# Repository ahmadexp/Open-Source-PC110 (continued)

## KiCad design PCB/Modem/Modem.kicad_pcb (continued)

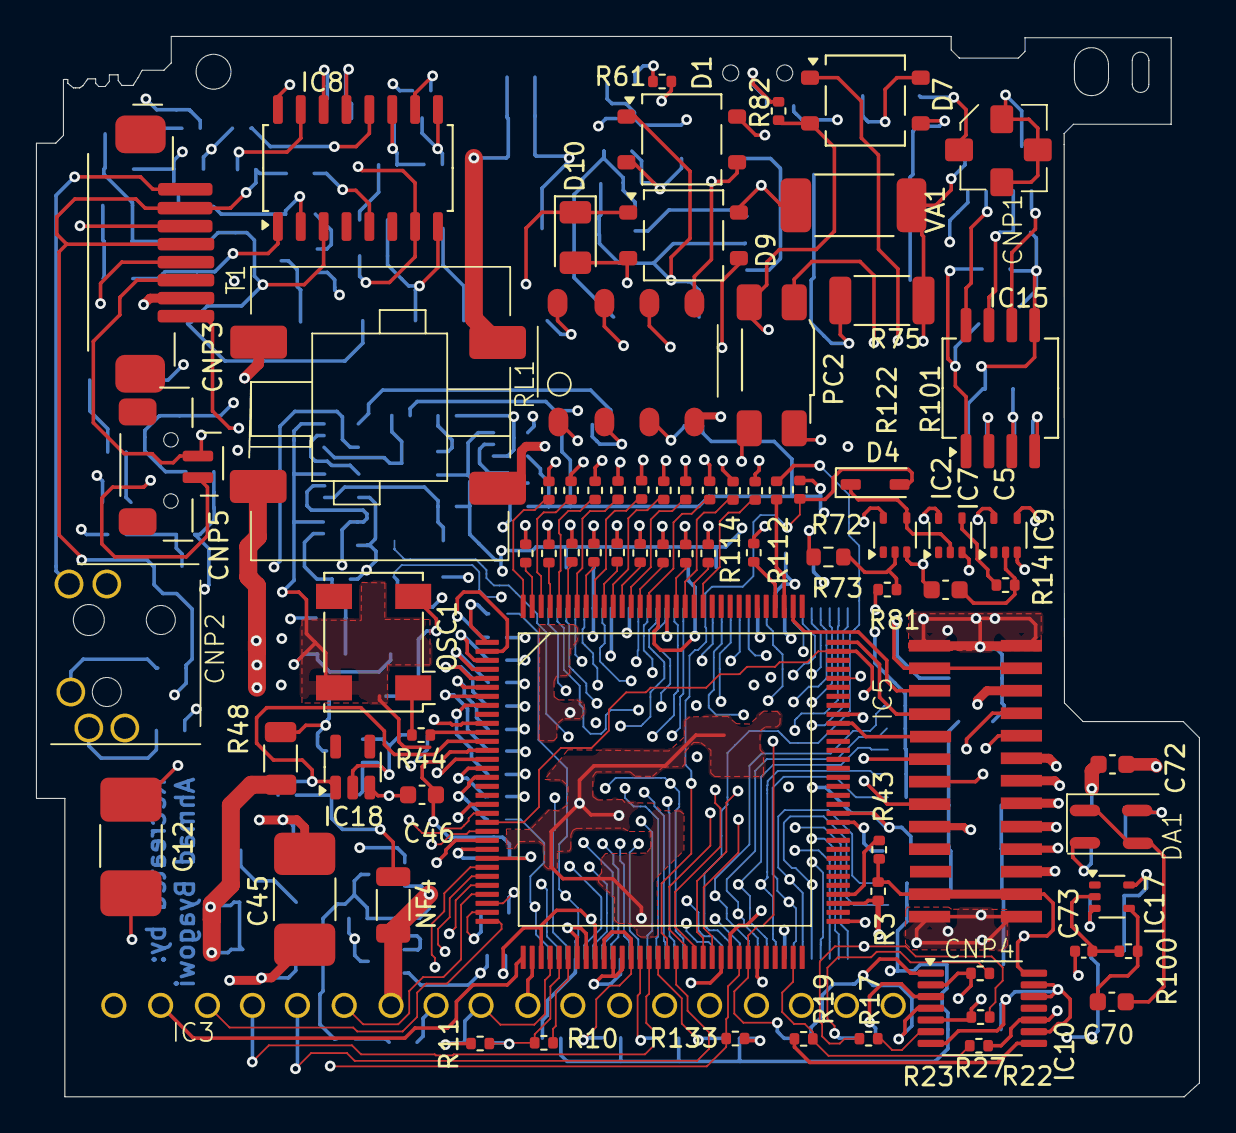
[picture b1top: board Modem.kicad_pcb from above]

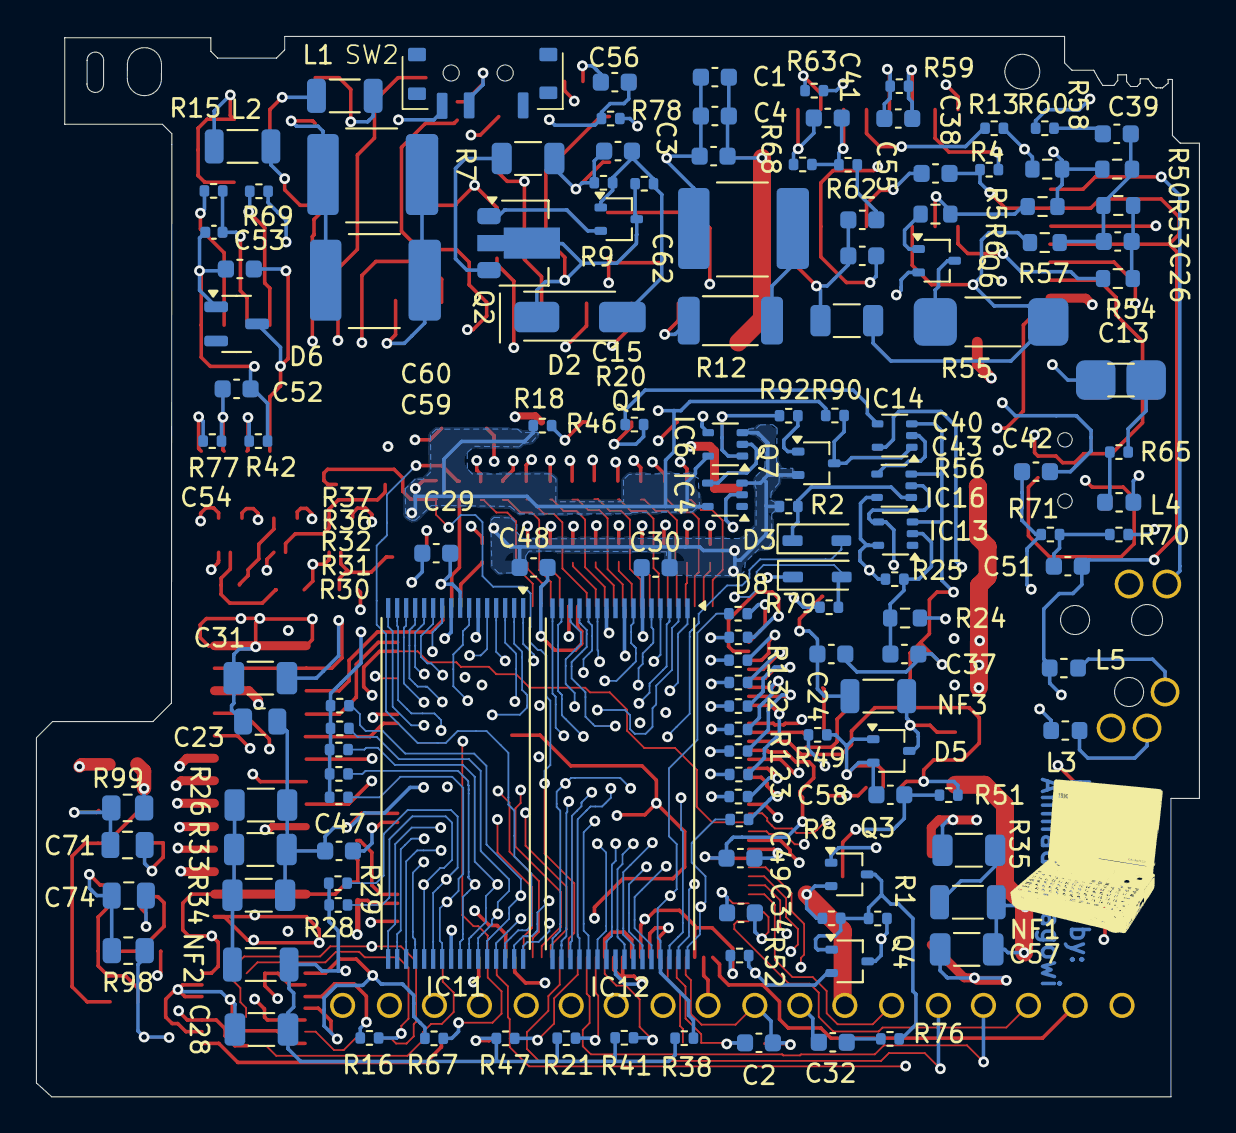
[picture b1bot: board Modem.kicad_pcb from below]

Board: 6 copper layers, 64.6 x 58.9 mm, 211 parts (136 on the bottom side), 206 nets.

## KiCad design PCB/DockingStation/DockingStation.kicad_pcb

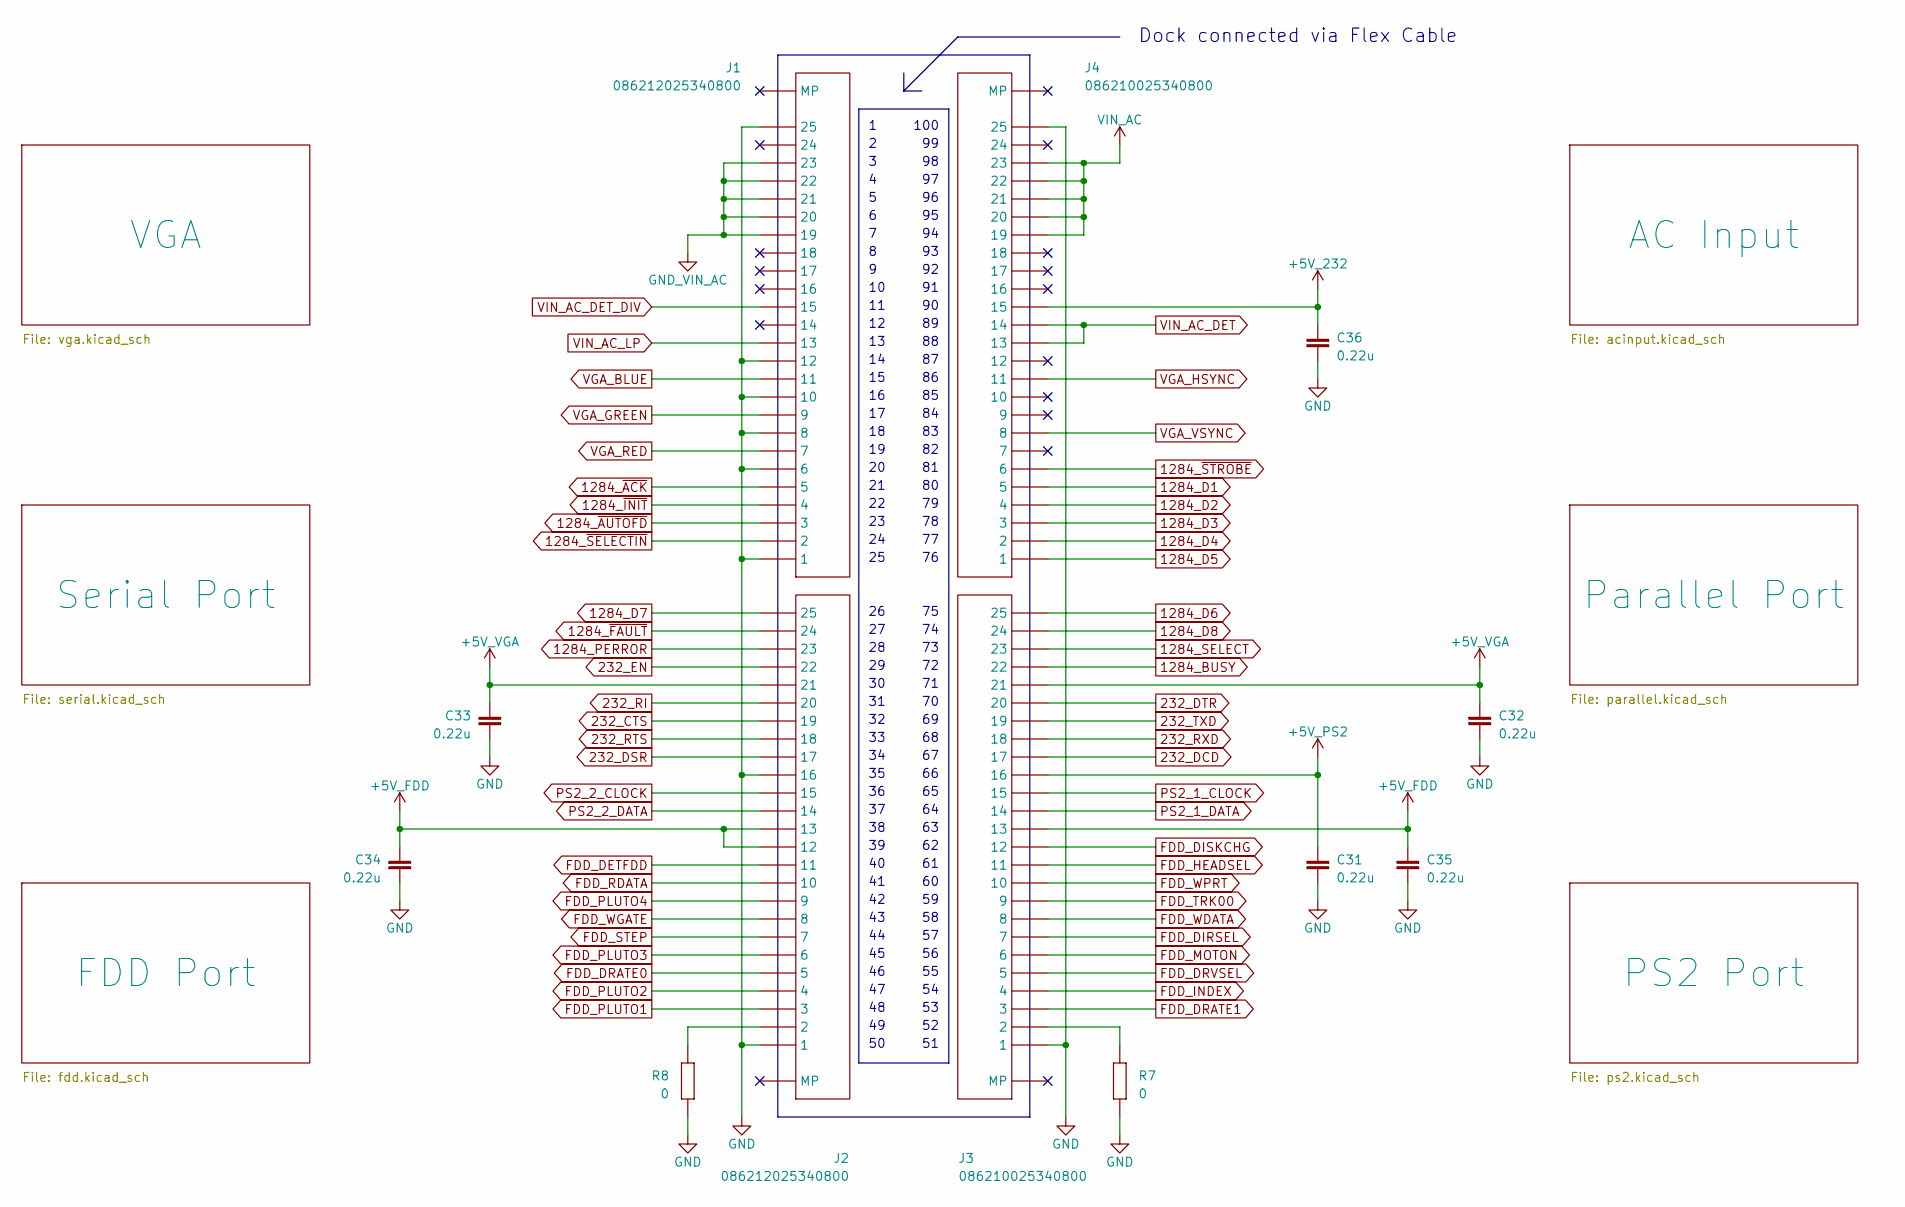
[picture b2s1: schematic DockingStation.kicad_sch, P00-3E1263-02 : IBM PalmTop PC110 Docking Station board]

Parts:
C31, C32, C33, C34, C35, C36: 0.22u
J1, J2: 086212025340800
J3, J4: 086210025340800
R7, R8: 0

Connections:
232_CTS: J2.19; also elsewhere on the board
232_DCD: J3.17; also elsewhere on the board
232_DSR: J2.17; also elsewhere on the board
232_DTR: J3.20; also elsewhere on the board
232_EN: J2.22; also elsewhere on the board
232_RI: J2.20; also elsewhere on the board
232_RTS: J2.18; also elsewhere on the board
232_RXD: J3.18; also elsewhere on the board
232_TXD: J3.19; also elsewhere on the board
1284_BUSY: J3.22; also elsewhere on the board
1284_D1: J4.5; also elsewhere on the board
1284_D2: J4.4; also elsewhere on the board
1284_D3: J4.3; also elsewhere on the board
1284_D4: J4.2; also elsewhere on the board
1284_D5: J4.1; also elsewhere on the board
1284_D6: J3.25; also elsewhere on the board
1284_D7: J2.25; also elsewhere on the board
1284_D8: J3.24; also elsewhere on the board
1284_PERROR: J2.23; also elsewhere on the board
1284_SELECT: J3.23; also elsewhere on the board
1284_~ACK: J1.5; also elsewhere on the board
1284_~AUTOFD: J1.3; also elsewhere on the board
1284_~FAULT: J2.24; also elsewhere on the board
1284_~INIT: J1.4; also elsewhere on the board
1284_~SELECTIN: J1.2; also elsewhere on the board
1284_~STROBE: J4.6; also elsewhere on the board
+5V_232: C36.2, J4.15; also elsewhere on the board
+5V_FDD: C34.2, C35.2, J2.12, J2.13, J3.13; also elsewhere on the board
+5V_PS2: C31.2, J3.16; also elsewhere on the board
+5V_VGA: C32.1, C33.1, J2.21, J3.21; also elsewhere on the board
FDD_DETFDD: J2.11; also elsewhere on the board
FDD_DIRSEL: J3.7; also elsewhere on the board
FDD_DISKCHG: J3.12; also elsewhere on the board
FDD_DRATE0: J2.5; also elsewhere on the board
FDD_DRATE1: J3.3; also elsewhere on the board
FDD_DRVSEL: J3.5; also elsewhere on the board
FDD_HEADSEL: J3.11; also elsewhere on the board
FDD_INDEX: J3.4; also elsewhere on the board
FDD_MOTON: J3.6; also elsewhere on the board
FDD_PLUTO1: J2.3; also elsewhere on the board
FDD_PLUTO2: J2.4; also elsewhere on the board
FDD_PLUTO3: J2.6; also elsewhere on the board
FDD_PLUTO4: J2.9; also elsewhere on the board
FDD_RDATA: J2.10; also elsewhere on the board
FDD_STEP: J2.7; also elsewhere on the board
FDD_TRK00: J3.9; also elsewhere on the board
FDD_WDATA: J3.8; also elsewhere on the board
FDD_WGATE: J2.8; also elsewhere on the board
FDD_WPRT: J3.10; also elsewhere on the board
GND: C31.1, C32.2, C33.2, C34.1, C35.1, C36.1, J1.1, J1.6, J1.8, J1.10, J1.12, J1.25, J2.1, J2.16, J3.1, J4.25, R7.2, R8.2; also elsewhere on the board
GND_VIN_AC: J1.19, J1.20, J1.21, J1.22, J1.23; also elsewhere on the board
unnamed: J2.2, R8.1
unnamed: J3.2, R7.1
PS2_1_CLOCK: J3.15; also elsewhere on the board
PS2_1_DATA: J3.14; also elsewhere on the board
PS2_2_CLOCK: J2.15; also elsewhere on the board
PS2_2_DATA: J2.14; also elsewhere on the board
VGA_BLUE: J1.11; also elsewhere on the board
VGA_GREEN: J1.9; also elsewhere on the board
VGA_HSYNC: J4.11; also elsewhere on the board
VGA_RED: J1.7; also elsewhere on the board
VGA_VSYNC: J4.8; also elsewhere on the board
VIN_AC: J4.19, J4.20, J4.21, J4.22, J4.23; also elsewhere on the board
VIN_AC_DET: J4.13, J4.14; also elsewhere on the board
VIN_AC_DET_DIV: J1.15; also elsewhere on the board
VIN_AC_LP: J1.13; also elsewhere on the board

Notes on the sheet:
100
Dock connected via Flex Cable

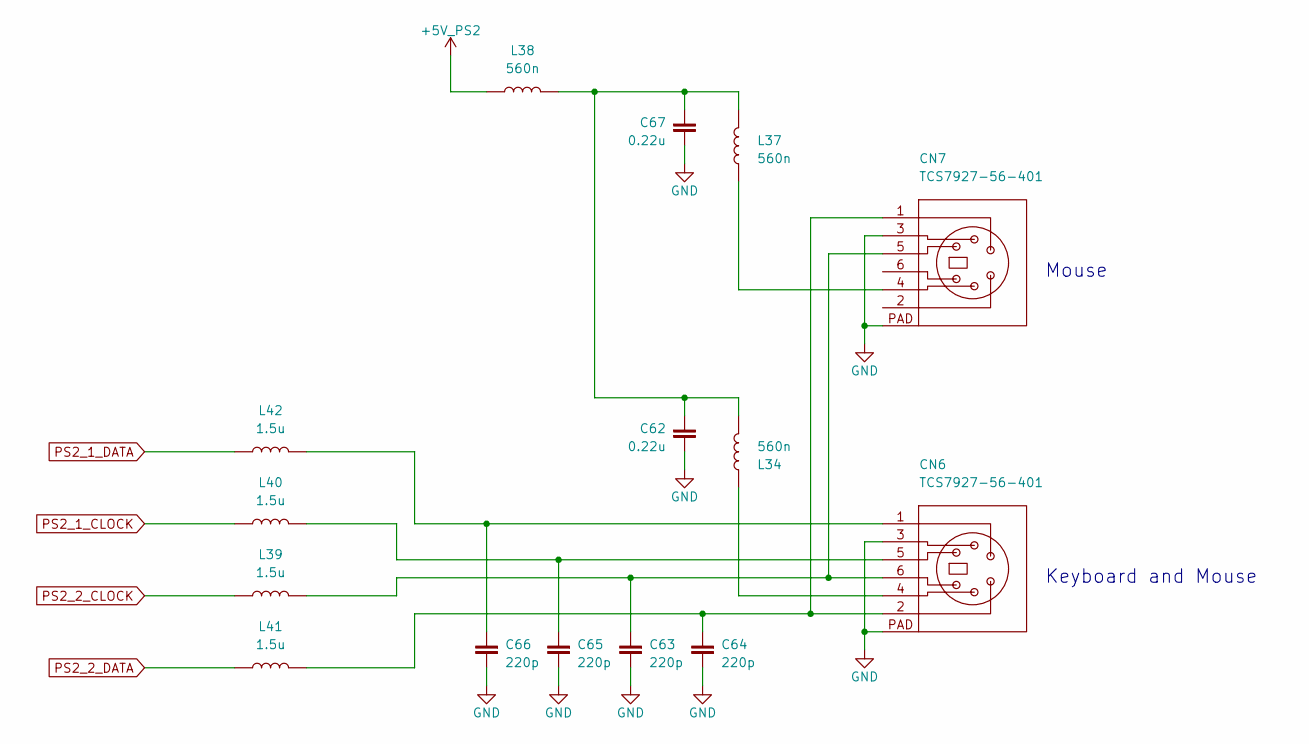
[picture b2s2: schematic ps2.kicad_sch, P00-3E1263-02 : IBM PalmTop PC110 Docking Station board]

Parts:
C62, C67: 0.22u
C63, C64, C65, C66: 220p
CN6, CN7: TCS7927-56-401
L34, L37, L38: 560n
L39, L40, L41, L42: 1.5u

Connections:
+5V_PS2: L38.2; also elsewhere on the board
GND: C62.2, C63.1, C64.1, C65.1, C66.1, C67.2, CN6.3, CN6.PAD (PDA), CN7.3, CN7.PAD (PDA); also elsewhere on the board
unnamed: C62.1, C67.1, L34.2, L37.2, L38.1
unnamed: C63.2, CN6.6, CN7.5, L39.1
unnamed: C64.2, CN6.2, CN7.1, L41.1
unnamed: C65.2, CN6.5, L40.1
unnamed: C66.2, CN6.1, L42.1
unnamed: CN6.4, L34.1
unnamed: CN7.4, L37.1
PS2_1_CLOCK: L40.2; also elsewhere on the board
PS2_1_DATA: L42.2; also elsewhere on the board
PS2_2_CLOCK: L39.2; also elsewhere on the board
PS2_2_DATA: L41.2; also elsewhere on the board

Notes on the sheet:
Mouse
Keyboard and Mouse

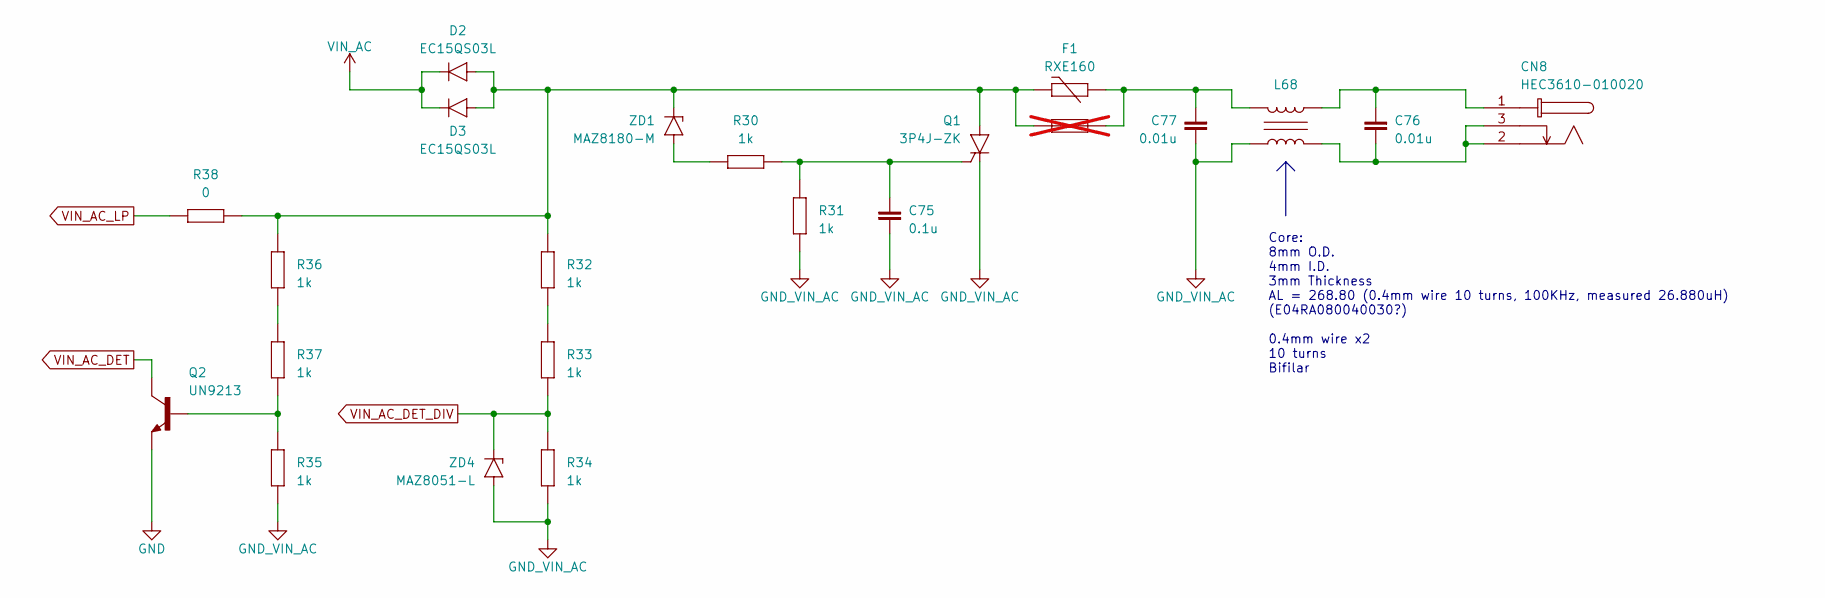
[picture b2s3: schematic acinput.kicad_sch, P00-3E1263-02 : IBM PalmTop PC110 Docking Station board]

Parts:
C75: 0.1u
C76, C77: 0.01u
CN8: HEC3610-010020
D2, D3: EC15QS03L
F1: RXE160
L68: (no value)
Q1: 3P4J-ZK
Q2: UN9213
R30, R31, R32, R33, R34, R35, R36, R37: 1k
R38: 0
SSFC1: not fitted
ZD1: MAZ8180-M
ZD4: MAZ8051-L

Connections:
GND: Q2.2 (E); also elsewhere on the board
GND_VIN_AC: C75.2, C77.2, L68.2, Q1.1 (C), R31.1, R34.1, R35.1, ZD4.2 (A); also elsewhere on the board
unnamed: C76.1, CN8.2, CN8.3, L68.1
unnamed: C76.2, CN8.1, L68.3
unnamed: C77.1, F1.1, L68.4, SSFC1.1
unnamed: D2.2 (A), D3.2 (A), F1.2, Q1.2 (A), R32.2, R36.2, R38.2, SSFC1.2, ZD1.1 (C)
unnamed: C75.1, Q1.3 (G), R30.1, R31.2
unnamed: Q2.1 (B), R35.2, R37.1
unnamed: R32.1, R33.2
unnamed: R36.1, R37.2
unnamed: R30.2, ZD1.2 (A)
VIN_AC: D2.1 (C), D3.1 (C); also elsewhere on the board
VIN_AC_DET: Q2.3 (C); also elsewhere on the board
VIN_AC_DET_DIV: R33.1, R34.2, ZD4.1 (C); also elsewhere on the board
VIN_AC_LP: R38.1; also elsewhere on the board

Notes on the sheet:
Core: 8mm O.D. 4mm I.D. 3mm Thickness AL = 268.80 (0.4mm wire 10 turns, 100KHz, measured 26.880uH) (E04RA080040030?) 0.4mm wire x2 10 turns Bifilar

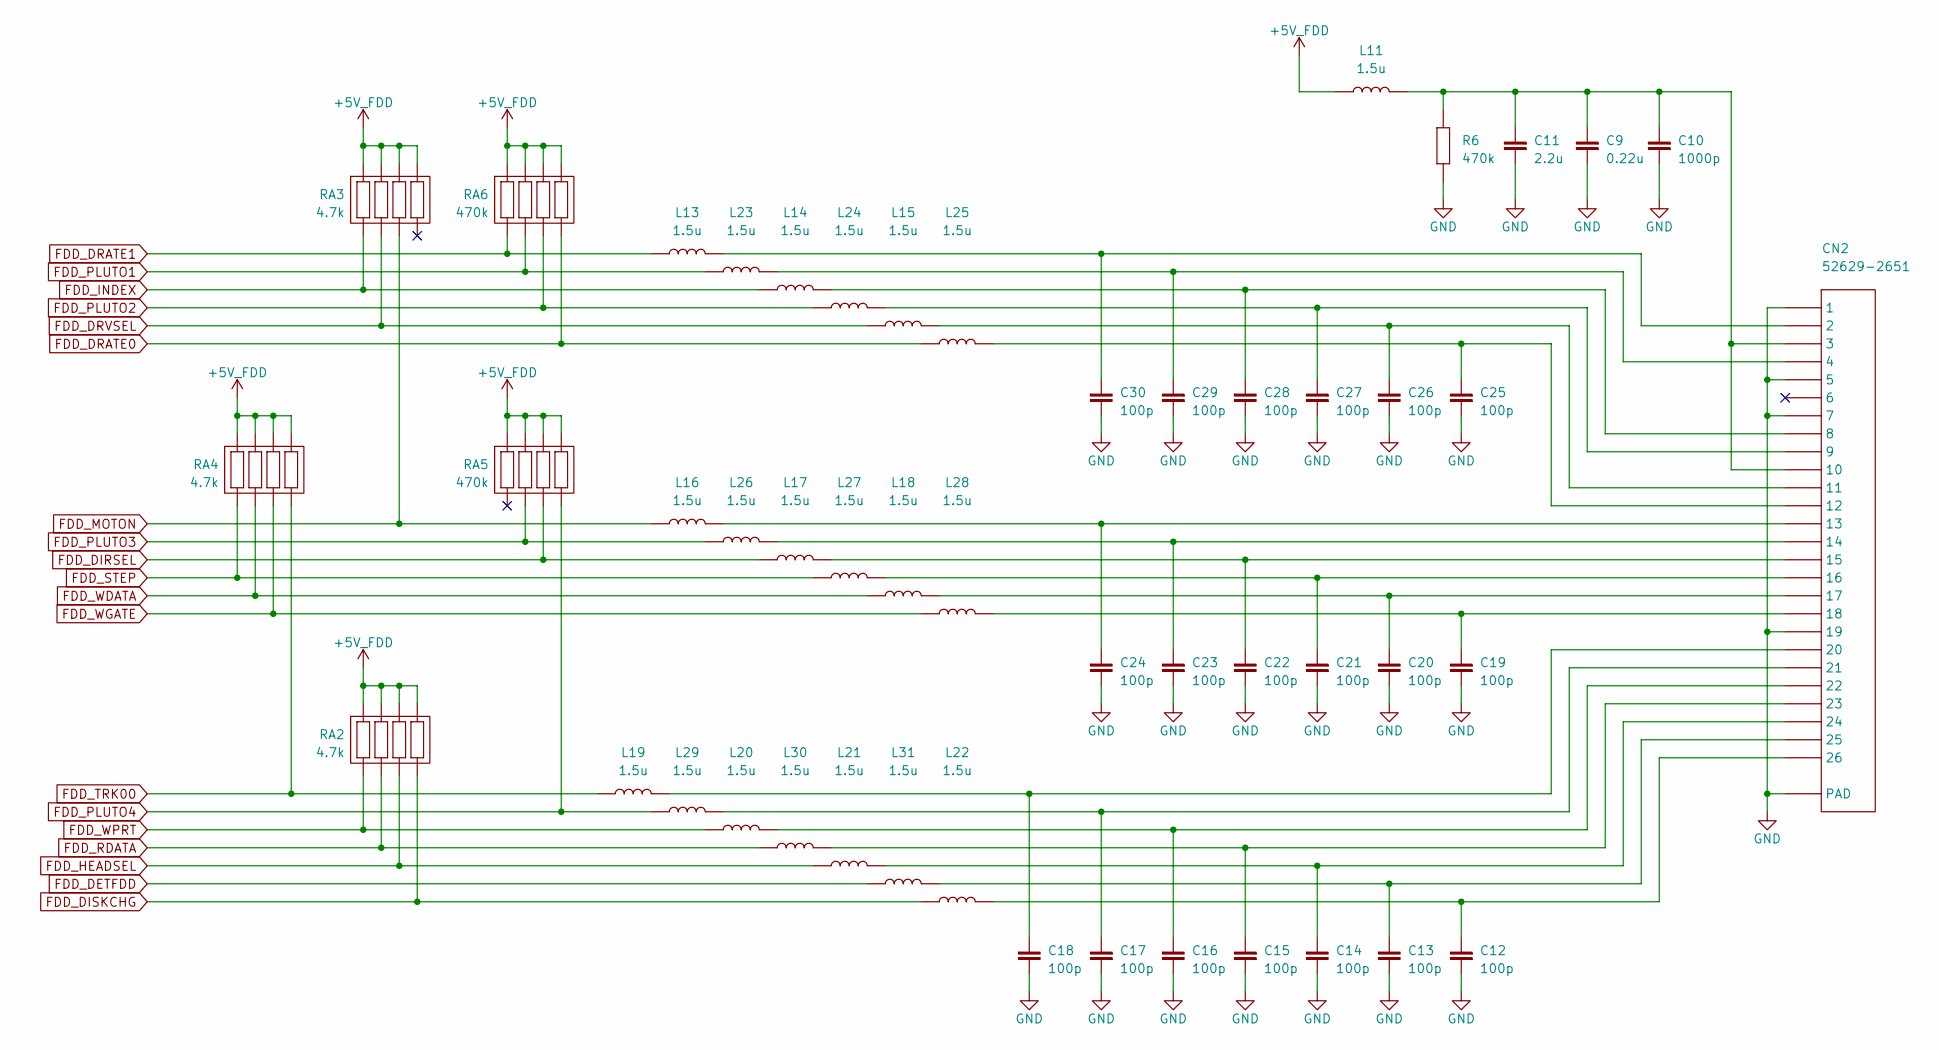
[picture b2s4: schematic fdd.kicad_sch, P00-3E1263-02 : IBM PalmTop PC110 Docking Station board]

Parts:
C9: 0.22u
C10: 1000p
C11: 2.2u
C12, C13, C14, C15, C16, C17, C18, C19, C20, C21, C22, C23, C24, C25, C26, C27, C28, C29, C30: 100p
CN2: 52629-2651
L11, L13, L14, L15, L16, L17, L18, L19, L20, L21, L22, L23, L24, L25, L26, L27, L28, L29, L30, L31: 1.5u
R6: 470k
RA2, RA3, RA4: 4.7k
RA5, RA6: 470k

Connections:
+5V_FDD: L11.1, RA2.1, RA2.2, RA2.3, RA2.4, RA3.1, RA3.2, RA3.3, RA3.4, RA4.1, RA4.2, RA4.3, RA4.4, RA5.1, RA5.2, RA5.3, RA5.4, RA6.1, RA6.2, RA6.3, RA6.4; also elsewhere on the board
FDD_DETFDD: L31.2; also elsewhere on the board
FDD_DIRSEL: L17.1, RA5.6; also elsewhere on the board
FDD_DISKCHG: L22.1, RA2.5; also elsewhere on the board
FDD_DRATE0: L25.1, RA6.5; also elsewhere on the board
FDD_DRATE1: L13.1, RA6.8; also elsewhere on the board
FDD_DRVSEL: L15.1, RA3.7; also elsewhere on the board
FDD_HEADSEL: L21.1, RA2.6; also elsewhere on the board
FDD_INDEX: L14.1, RA3.8; also elsewhere on the board
FDD_MOTON: L16.1, RA3.6; also elsewhere on the board
FDD_PLUTO1: L23.1, RA6.7; also elsewhere on the board
FDD_PLUTO2: L24.1, RA6.6; also elsewhere on the board
FDD_PLUTO3: L26.1, RA5.7; also elsewhere on the board
FDD_PLUTO4: L29.1, RA5.5; also elsewhere on the board
FDD_RDATA: L30.1, RA2.7; also elsewhere on the board
FDD_STEP: L27.1, RA4.8; also elsewhere on the board
FDD_TRK00: L19.1, RA4.5; also elsewhere on the board
FDD_WDATA: L18.1, RA4.7; also elsewhere on the board
FDD_WGATE: L28.1, RA4.6; also elsewhere on the board
FDD_WPRT: L20.1, RA2.8; also elsewhere on the board
GND: C9.1, C10.1, C11.1, C12.1, C13.2, C14.2, C15.1, C16.2, C17.1, C18.2, C19.1, C20.2, C21.1, C22.2, C23.1, C24.2, C25.1, C26.2, C27.1, C28.2, C29.1, C30.2, CN2.1, CN2.3 (5), CN2.4 (7), CN2.10 (19), CN2.PAD, R6.1; also elsewhere on the board
unnamed: C12.2, CN2.26, L22.2
unnamed: C30.1, CN2.14 (2), L13.2
unnamed: C29.2, CN2.15 (4), L23.2
unnamed: C28.1, CN2.17 (8), L14.2
unnamed: C27.2, CN2.5 (9), L24.2
unnamed: C9.2, C10.2, C11.2, CN2.2 (3), CN2.18 (10), L11.2, R6.2
unnamed: C26.1, CN2.6 (11), L15.2
unnamed: C25.2, CN2.19 (12), L25.2
unnamed: C24.1, CN2.7 (13), L16.2
unnamed: C23.2, CN2.20 (14), L26.2
unnamed: C22.1, CN2.8 (15), L17.2
unnamed: C21.2, CN2.21 (16), L27.2
unnamed: C20.1, CN2.9 (17), L18.2
unnamed: C19.2, CN2.22 (18), L28.2
unnamed: C18.1, CN2.23 (20), L19.2
unnamed: C17.2, CN2.11 (21), L29.2
unnamed: C16.1, CN2.24 (22), L20.2
unnamed: C15.2, CN2.12 (23), L30.2
unnamed: C14.1, CN2.25 (24), L21.2
unnamed: C13.1, CN2.13 (25), L31.1

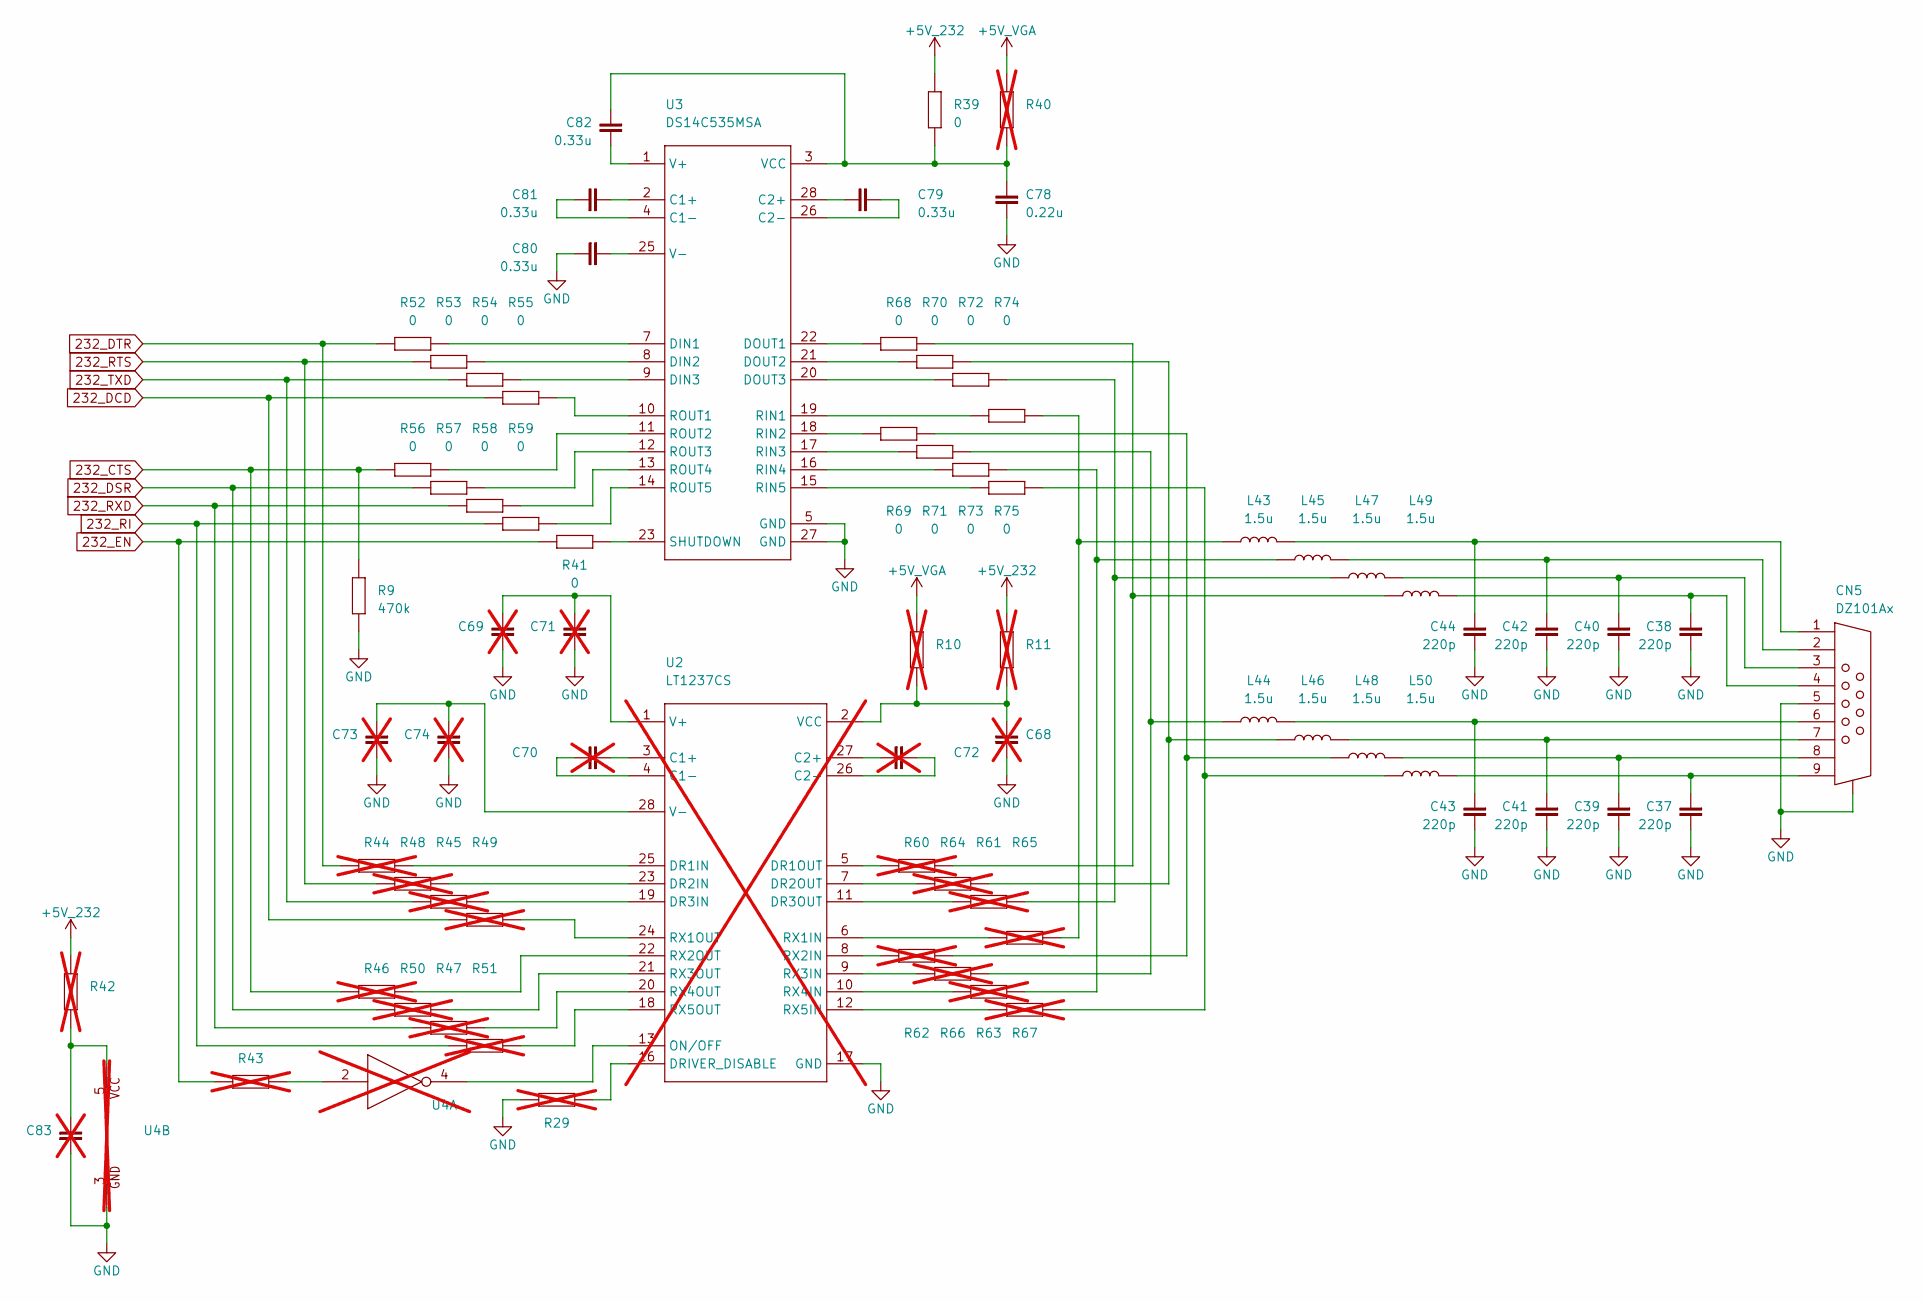
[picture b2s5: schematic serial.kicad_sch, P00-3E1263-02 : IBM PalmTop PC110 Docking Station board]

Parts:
C37, C38, C39, C40, C41, C42, C43, C44: 220p
C68, C69, C70, C71, C72, C73, C74, C83: not fitted
C78: 0.22u
C79, C80, C81, C82: 0.33u
CN5: DZ101Ax
L43, L44, L45, L46, L47, L48, L49, L50: 1.5u
R9: 470k
R10, R11, R29, R40, R42, R43, R44, R45, R46, R47, R48, R49, R50, R51, R60, R61, R62, R63, R64, R65, R66, R67: not fitted
R39, R41, R52, R53, R54, R55, R56, R57, R58, R59, R68, R69, R70, R71, R72, R73, R74, R75: 0
U2: LT1237CS; not fitted
U3: DS14C535MSA
U4: not fitted

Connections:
232_CTS: R9.1, R46.2, R56.1; also elsewhere on the board
232_DCD: R49.2, R55.1; also elsewhere on the board
232_DSR: R50.2, R57.1; also elsewhere on the board
232_DTR: R44.2, R52.1; also elsewhere on the board
232_EN: R41.1, R43.2; also elsewhere on the board
232_RI: R51.1, R59.2; also elsewhere on the board
232_RTS: R48.2, R53.1; also elsewhere on the board
232_RXD: R47.2, R58.1; also elsewhere on the board
232_TXD: R45.2, R54.1; also elsewhere on the board
+5V_232: R11.1, R39.1, R42.1; also elsewhere on the board
+5V_VGA: R10.2, R40.2; also elsewhere on the board
GND: C37.2, C38.2, C39.2, C40.2, C41.2, C42.1, C43.2, C44.2, C68.2, C69.2, C71.2, C73.2, C74.2, C78.1, C80.2, C83.1, CN5.0, CN5.5, R9.2, R29.1, U2.17 (GND), U3.5 (GND), U3.27 (GND), U4.3 (GND); also elsewhere on the board
unnamed: C37.1, CN5.9, L50.2
unnamed: C38.1, CN5.4, L49.2
unnamed: C39.1, CN5.8, L48.2
unnamed: C40.1, CN5.3, L47.2
unnamed: C41.1, CN5.7, L46.2
unnamed: C42.2, CN5.2, L45.2
unnamed: C43.1, CN5.6, L44.2
unnamed: C44.1, CN5.1, L43.2
unnamed: L43.1, R65.1, R74.2
unnamed: L44.1, R66.1, R71.2
unnamed: L45.1, R63.1, R73.2
unnamed: L46.1, R64.1, R70.2
unnamed: L47.1, R61.1, R72.2
unnamed: L48.1, R62.1, R69.2
unnamed: L49.1, R60.1, R68.2
unnamed: L50.1, R67.1, R75.2
unnamed: C70.2, U2.3 (C1+)
unnamed: C70.1, U2.4 (C1-)
unnamed: C72.2, U2.27 (C2+)
unnamed: C72.1, U2.26 (C2-)
unnamed: R44.1, U2.25 (DR1IN)
unnamed: R60.2, U2.5 (DR1OUT)
unnamed: R48.1, U2.23 (DR2IN)
unnamed: R64.2, U2.7 (DR2OUT)
unnamed: R45.1, U2.19 (DR3IN)
unnamed: R61.2, U2.11 (DR3OUT)
unnamed: R29.2, U2.16 (DRIVER_DISABLE)
unnamed: U2.13 (ON/OFF), U4.4 (O)
unnamed: R65.2, U2.6 (RX1IN)
unnamed: R49.1, U2.24 (RX1OUT)
unnamed: R62.2, U2.8 (RX2IN)
unnamed: R46.1, U2.22 (RX2OUT)
unnamed: R66.2, U2.9 (RX3IN)
unnamed: R50.1, U2.21 (RX3OUT)
unnamed: R63.2, U2.10 (RX4IN)
unnamed: R47.1, U2.20 (RX4OUT)
unnamed: R67.2, U2.12 (RX5IN)
unnamed: R51.2, U2.18 (RX5OUT)
unnamed: C69.1, C71.1, U2.1 (V+)
unnamed: C73.1, C74.1, U2.28 (V-)
unnamed: C68.1, R10.1, R11.2, U2.2 (VCC)
unnamed: C81.2, U3.2 (C1+)
unnamed: C81.1, U3.4 (C1-)
unnamed: C79.1, U3.28 (C2+)
unnamed: C79.2, U3.26 (C2-)
unnamed: R52.2, U3.7 (DIN1)
unnamed: R53.2, U3.8 (DIN2)
unnamed: R54.2, U3.9 (DIN3)
unnamed: R68.1, U3.22 (DOUT1)
unnamed: R70.1, U3.21 (DOUT2)
unnamed: R72.1, U3.20 (DOUT3)
unnamed: R74.1, U3.19 (RIN1)
unnamed: R69.1, U3.18 (RIN2)
unnamed: R71.1, U3.17 (RIN3)
unnamed: R73.1, U3.16 (RIN4)
unnamed: R75.1, U3.15 (RIN5)
unnamed: R55.2, U3.10 (ROUT1)
unnamed: R56.2, U3.11 (ROUT2)
unnamed: R57.2, U3.12 (ROUT3)
unnamed: R58.2, U3.13 (ROUT4)
unnamed: R59.1, U3.14 (ROUT5)
unnamed: R41.2, U3.23 (SHUTDOWN)
unnamed: C82.2, U3.1 (V+)
unnamed: C80.1, U3.25 (V-)
unnamed: C78.2, C82.1, R39.2, R40.1, U3.3 (VCC)
unnamed: R43.1, U4.2 (I)
unnamed: C83.2, R42.2, U4.5 (VCC)

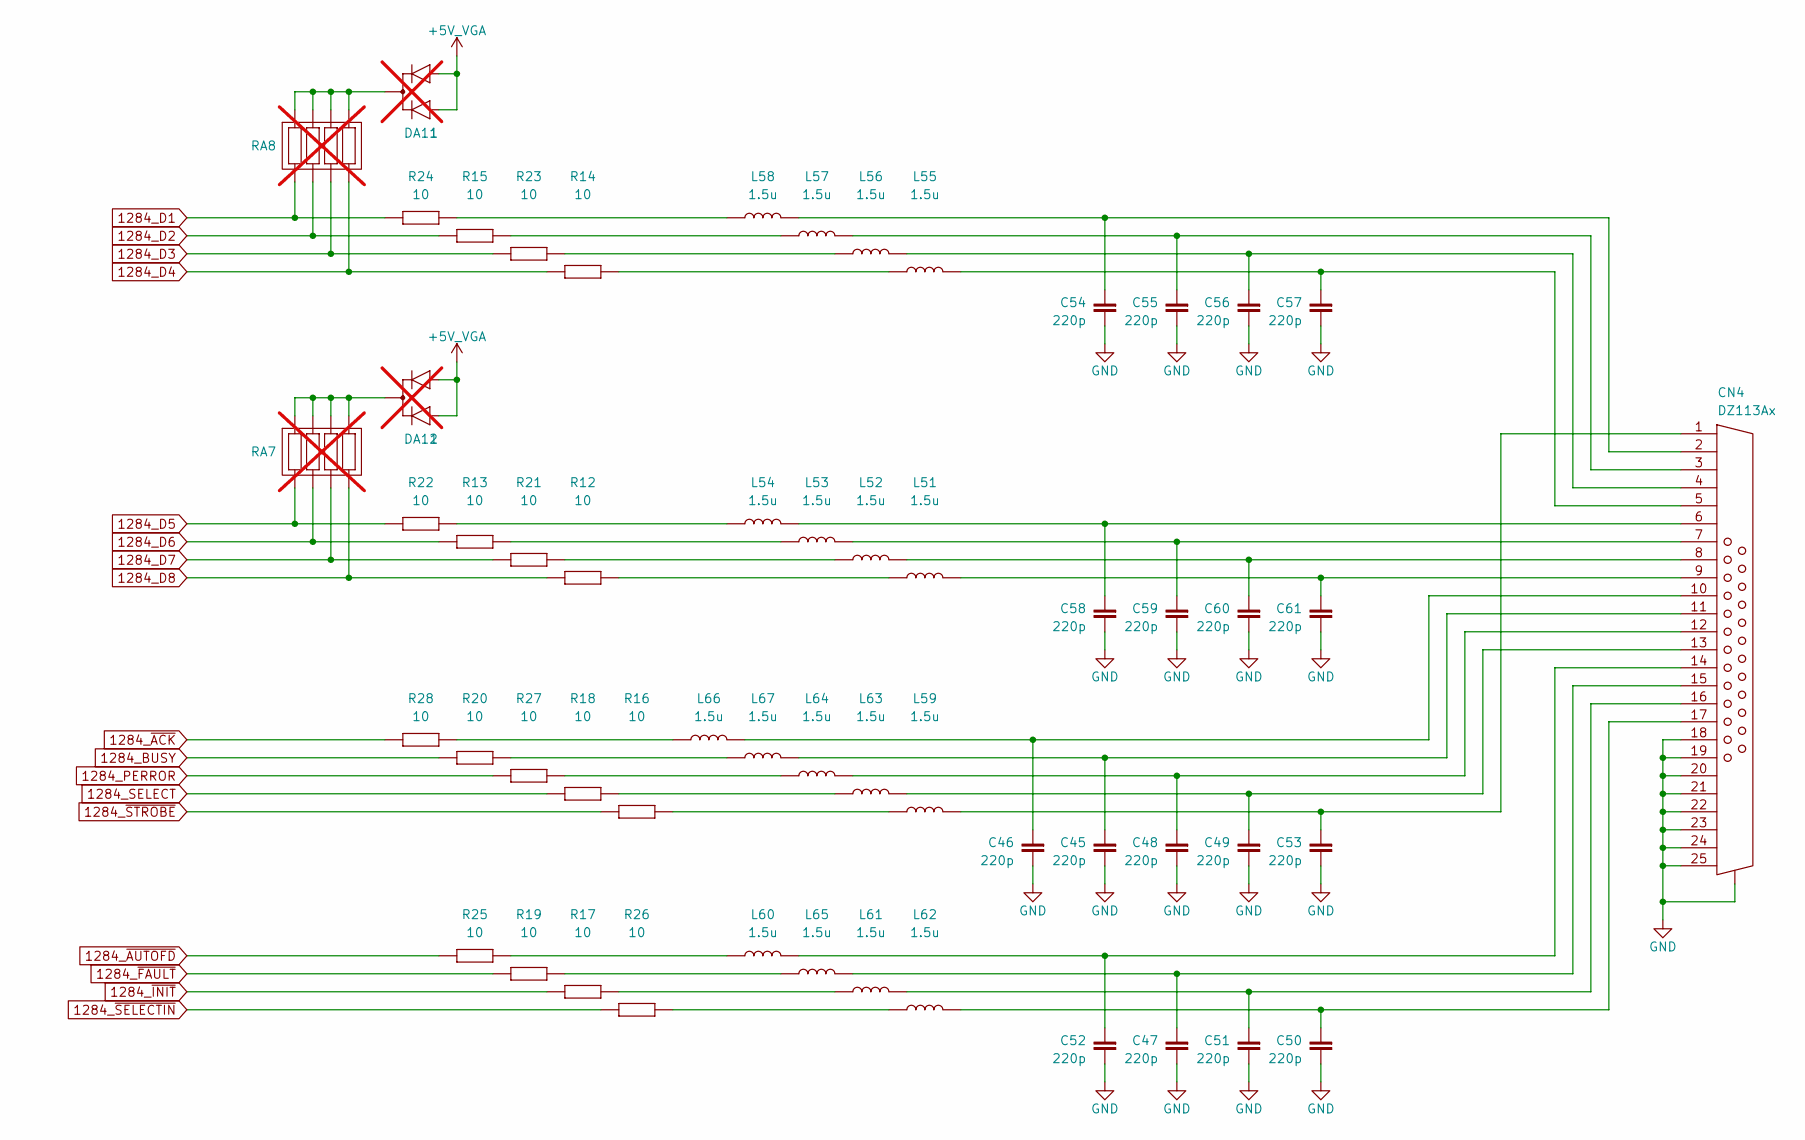
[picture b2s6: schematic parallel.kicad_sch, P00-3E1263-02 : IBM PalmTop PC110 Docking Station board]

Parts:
C45, C46, C47, C48, C49, C50, C51, C52, C53, C54, C55, C56, C57, C58, C59, C60, C61: 220p
CN4: DZ113Ax
DA11, DA12: 1; not fitted
L51, L52, L53, L54, L55, L56, L57, L58, L59, L60, L61, L62, L63, L64, L65, L66, L67: 1.5u
R12, R13, R14, R15, R16, R17, R18, R19, R20, R21, R22, R23, R24, R25, R26, R27, R28: 10
RA7, RA8: not fitted

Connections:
1284_BUSY: R20.1; also elsewhere on the board
1284_D1: R24.1, RA8.8; also elsewhere on the board
1284_D2: R15.1, RA8.7; also elsewhere on the board
1284_D3: R23.1, RA8.6; also elsewhere on the board
1284_D4: R14.1, RA8.5; also elsewhere on the board
1284_D5: R22.1, RA7.8; also elsewhere on the board
1284_D6: R13.1, RA7.7; also elsewhere on the board
1284_D7: R21.2, RA7.6; also elsewhere on the board
1284_D8: R12.1, RA7.5; also elsewhere on the board
1284_PERROR: R27.1; also elsewhere on the board
1284_SELECT: R18.1; also elsewhere on the board
1284_~ACK: R28.1; also elsewhere on the board
1284_~AUTOFD: R25.1; also elsewhere on the board
1284_~FAULT: R19.1; also elsewhere on the board
1284_~INIT: R17.1; also elsewhere on the board
1284_~SELECTIN: R26.1; also elsewhere on the board
1284_~STROBE: R16.1; also elsewhere on the board
+5V_VGA: DA11.1 (A1), DA11.2 (A2), DA12.1 (A1), DA12.2 (A2); also elsewhere on the board
GND: C45.1, C46.1, C47.1, C48.1, C49.1, C50.1, C51.1, C52.1, C53.1, C54.1, C55.1, C56.1, C57.1, C58.1, C59.1, C60.1, C61.1, CN4.0, CN4.18, CN4.19, CN4.20, CN4.21, CN4.22, CN4.23, CN4.24, CN4.25; also elsewhere on the board
unnamed: C45.2, CN4.11, L67.2
unnamed: C46.2, CN4.10, L66.2
unnamed: C47.2, CN4.15, L65.2
unnamed: C48.2, CN4.12, L64.2
unnamed: C49.2, CN4.13, L63.2
unnamed: C50.2, CN4.17, L62.2
unnamed: C51.2, CN4.16, L61.2
unnamed: C52.2, CN4.14, L60.2
unnamed: C53.2, CN4.1, L59.2
unnamed: C54.2, CN4.2, L58.2
unnamed: C55.2, CN4.3, L57.2
unnamed: C56.2, CN4.4, L56.2
unnamed: C57.2, CN4.5, L55.2
unnamed: C58.2, CN4.6, L54.2
unnamed: C59.2, CN4.7, L53.2
unnamed: C60.2, CN4.8, L52.2
unnamed: C61.2, CN4.9, L51.2
unnamed: DA11.3 (C), RA8.1, RA8.2, RA8.3, RA8.4
unnamed: DA12.3 (C), RA7.1, RA7.2, RA7.3, RA7.4
unnamed: L51.1, R12.2
unnamed: L52.1, R21.1
unnamed: L53.1, R13.2
unnamed: L54.1, R22.2
unnamed: L55.1, R14.2
unnamed: L56.1, R23.2
unnamed: L57.1, R15.2
unnamed: L58.1, R24.2
unnamed: L59.1, R16.2
unnamed: L60.1, R25.2
unnamed: L61.1, R17.2
unnamed: L62.1, R26.2
unnamed: L63.1, R18.2
unnamed: L64.1, R27.2
unnamed: L65.1, R19.2
unnamed: L66.1, R28.2
unnamed: L67.1, R20.2
